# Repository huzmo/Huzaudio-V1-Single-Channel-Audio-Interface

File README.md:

# Huzaudio V1 - Single-Channel-Audio-Interface
The Huzaudio V1 can record musical instruments such as an electric or bass guitar through a standard 1/4" jack onto a computer through a USB-A port. 
|||
|:-:|:-:|

## Hardware
In order to select the right components, I created a diagram that depicted the process needed to complete the task at a high level and then found suitable ICs for each central task. These ICs served as "nodes" and related components and circuitry were selected in reference to manufacturer data sheets. Each component must be a suitable size to solder by hand but also small enough to maintain a compact form factor. 

The PCB was designed using KiCad, a free and open source EDA which provided the tools necessary to design my circuit. The schematic was designed to provide a lower-level representation of the initial flowchart and set the groundwork for a reliable PCB. Each of the squares on the above chart has been "translated" into circuitry and complementary components, such as decoupling capacitors and resistors, have been added. 

The main issue when it comes to mixed signal boards is signal integrity. Knowing this, a great amount of research was conducted to ensure that my board was able to protect the sensitive analog inputs. A 4-layer board was chosen with the following stackup:
| Layer    |   Purpose      |
| -------- |        ------- |
| Layer 1  | Analog Signal  |
| Layer 2  |  Power Plane   |
| Layer 3  |  Ground Plane  |
| Layer 4  | Digital Signal |

The ground plane in between the two signal layers ensures that they are shielded from one another while also providing a short current return path. Analog and digital components are physically segregated from one another, and the ADC serves as a bridge between the two signal types. The above considerations, as well as low-noise ICs ensure that the instrument signal receives little disruption throughout the circuit. 

## Software
Firmware for the audio interface must receive the converted digital signal via I2C from the analog-digital converter and send appropriately formatted packets to the computer. Software is written in C on the STM32F103C8T6 using the STM32CUBEIDE. The firmware is currently in development.

## Mechanical
The design for the case is straightforward to ensure functionality. An ample amount of room is provided to ensure that all components fit inside. To shield from EMI, the inside of the case is coated in a conductive material to ensure that EMI cannot leak nor enter and disrupt the sensitive analog signals.

## Simulation
To ensure my design worked before ordering the board, I ran some simulations using KiCad's built-in SPICE simulator. I tested if the input voltage regulators ensured stable power delivery and that the guitar input signal was amplified correctly as seen below.

## Next Steps
The design for this product was completed during an extended break from university and the prototyping for this project is projected to be held during the following semester break.

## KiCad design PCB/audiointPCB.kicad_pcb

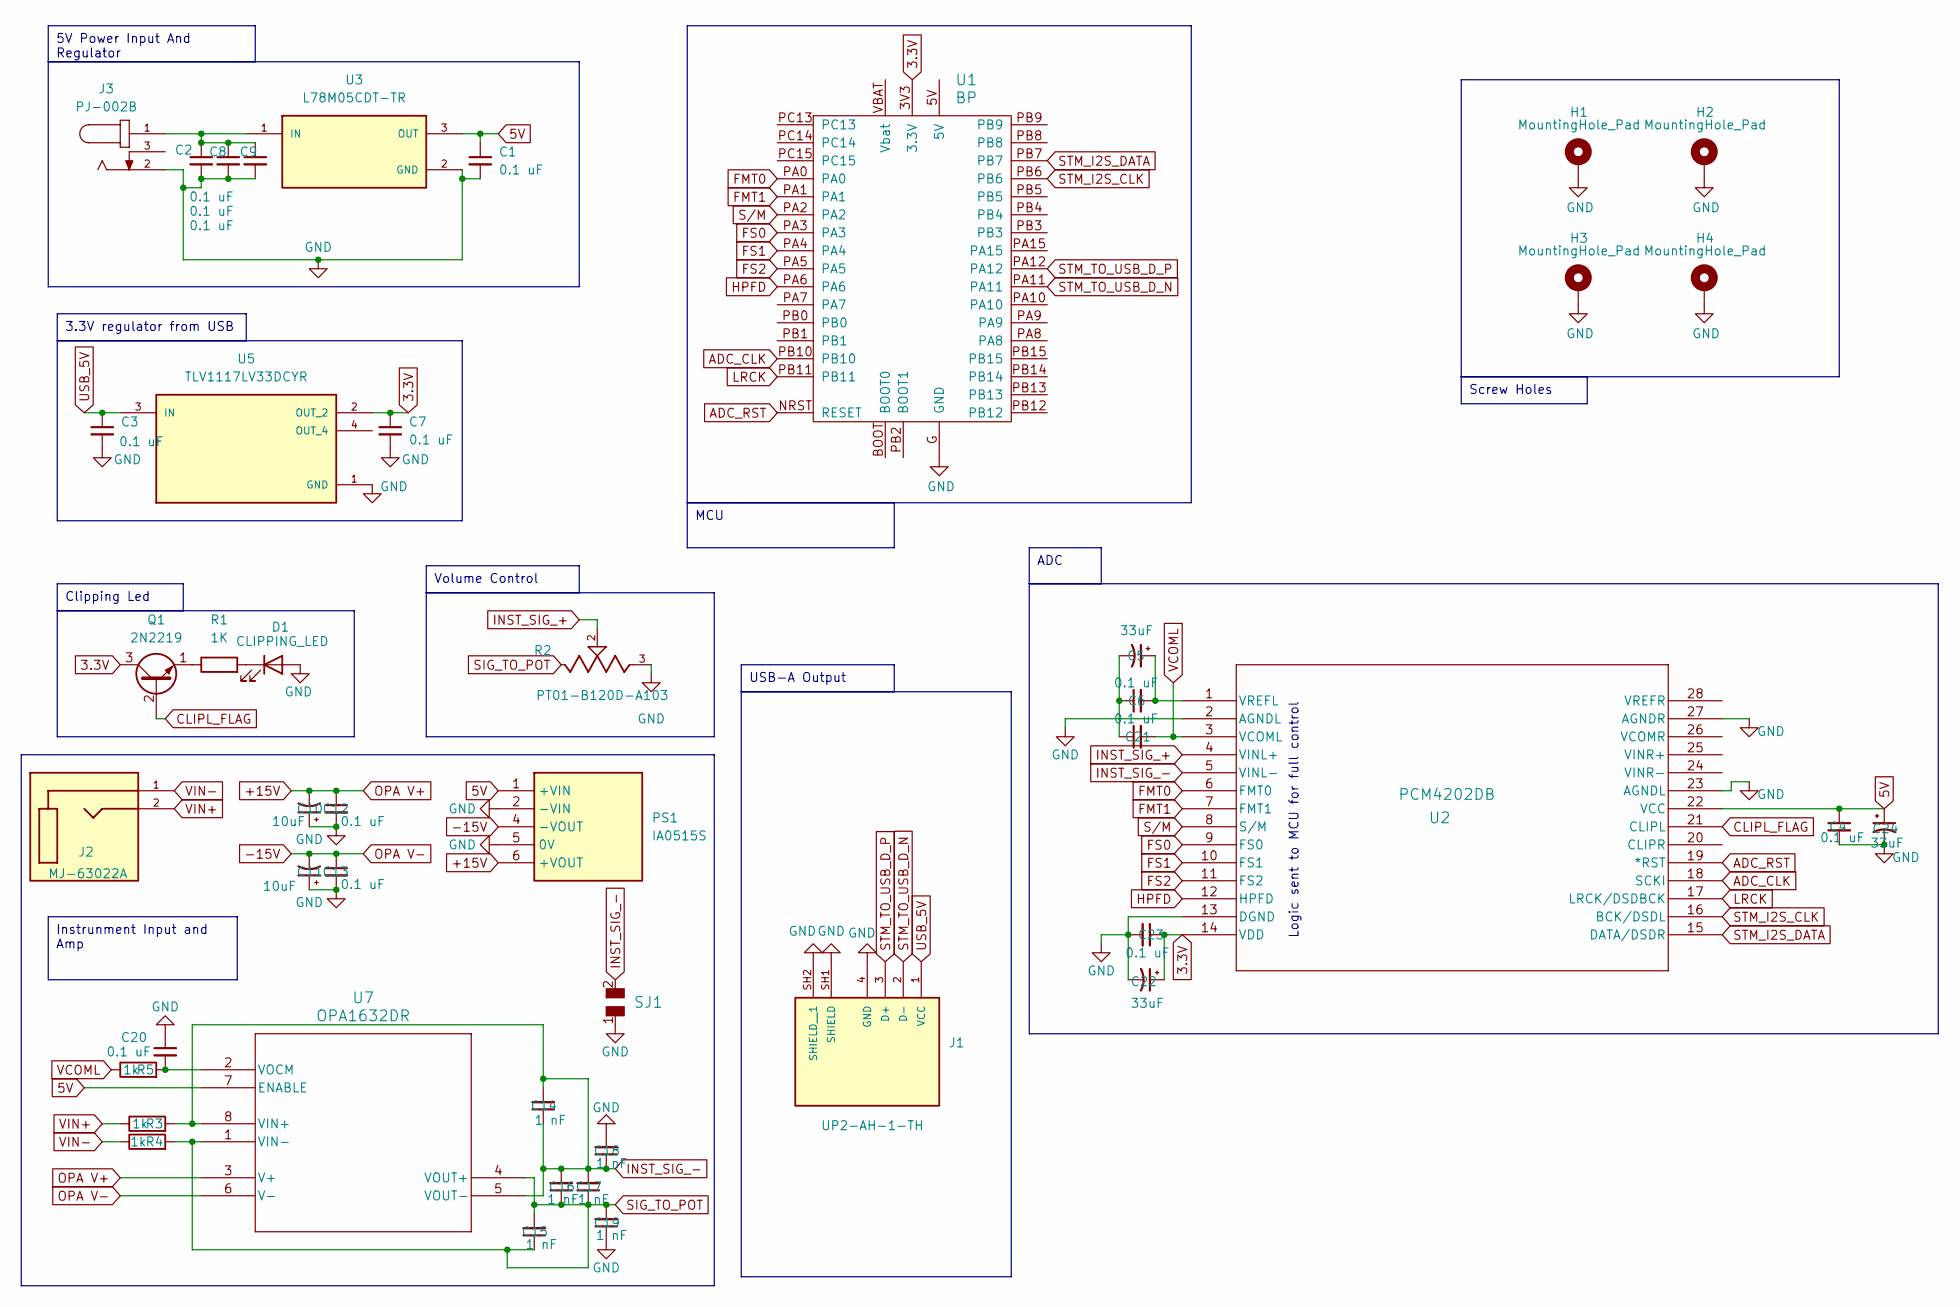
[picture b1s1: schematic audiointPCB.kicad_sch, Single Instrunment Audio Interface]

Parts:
C1, C2, C3, C4, C6, C7, C8, C9, C12, C13, C20, C21, C23: 0.1 uF; CAP_B32529_02.5X06.5X07.3_TDK
C5, C22, C24: 33uF; CAP_EEFK_C_PAN-L
C10, C11: 10uF; CAPC3216X180N
C14, C15, C16, C17, C18, C19: 1 nF; K104K10X7RF5UH5_VIS
D1: CLIPPING_LED; WL-TMRC_3MM
H1, H2, H3, H4: MountingHole_Pad; MountingHole_2mm
J1: UP2-AH-1-TH; CUI_UP2-AH-1-TH; PARTREV 1.05
J2: MJ-63022A; CUI_MJ-63022A; PARTREV 1.0
J3: PJ-002B; CUI_PJ-002B
PS1: IA0515S; Manufacturer_Part_Number IA0515S
Q1: 2N2219; TO-39-3
R1: 1K; RC1206N_YAG
R2: PT01-B120D-A103; TRIM_PT01-B120D-A103; PARTREV 1.0
R3, R4, R5: 1k; RC1206N_YAG
SJ1: SOLDER_JUMPER; SolderJumper-2_P1.3mm_Open_Pad1.0x1.5mm
U1: BP; blue_pill
U2: PCM4202DB; DB28
U3: L78M05CDT-TR; VREG_L78M05CDT-TR; PARTREV 24
U5: TLV1117LV33DCYR; VREG_TLV1117LV33DCYR; PARTREV B
U7: OPA1632DR; D8

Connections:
3.3V: C7.1, C22.1, C23.1, Q1.3 (C), U1.3V3 (3.3V), U2.14 (VDD), U5.2 (OUT_2)
5V: C1.1, C4.1, C24.1, PS1.1 (+VIN), U2.22 (VCC), U3.3 (OUT), U7.7 (ENABLE)
+15V: C10.2, C12.1, PS1.6 (+VOUT), U7.3 (V+)
-15V: C11.2, C13.1, PS1.4 (-VOUT), U7.6 (V-)
ADC_CLK: U1.PB10, U2.18 (SCKI)
ADC_RST: U1.NRST (RESET), U2.19 (*RST)
CLIPL_FLAG: Q1.2 (B), U2.21 (CLIPL)
FMT0: U1.PA0, U2.6 (FMT0)
FMT1: U1.PA1, U2.7 (FMT1)
FS0: U1.PA3, U2.9 (FS0)
FS1: U1.PA4, U2.10 (FS1)
FS2: U1.PA5, U2.11 (FS2)
GND: C1.2, C2.2, C3.2, C4.2, C7.2, C8.2, C9.2, C10.1, C11.1, C12.2, C13.2, C18.2, C19.1, C20.1, C22.2, C23.2, C24.2, D1.2 (A), H1.1, H2.1, H3.1, H4.1, J1.4 (GND), J1.SH1 (SHIELD), J1.SH2 (SHIELD__1), J3.2, PS1.2 (-VIN), PS1.5 (0V), R2.3, SJ1.1, U1.G (GND), U2.2 (AGNDL), U2.13 (DGND), U2.23 (AGNDL), U2.27 (AGNDR), U3.2 (GND), U5.1 (GND)
HPFD: U1.PA6, U2.12 (HPFD)
INST_SIG_+: R2.2, U2.4 (VINL+)
INST_SIG_-: C14.1, C14.2, C16.2, C17.2, C18.1, R3.2, SJ1.2, U2.5 (VINL-), U7.5 (VOUT-), U7.8 (VIN+)
LRCK: U1.PB11, U2.17 (LRCK/DSDBCK)
unnamed: C5.2, C6.1, C21.1
unnamed: D1.1 (K), R1.2
unnamed: Q1.1 (E), R1.1
unnamed: C5.1, C6.2, U2.1 (VREFL)
unnamed: C2.1, C8.1, C9.1, J3.1, U3.1 (IN)
unnamed: C20.2, R5.2, U7.2 (VOCM)
SIG_TO_POT: C15.1, C15.2, C16.1, C17.1, C19.2, R4.2, U7.1 (VIN-), U7.4 (VOUT+)
STM_I2S_CLK: U1.PB6, U2.16 (BCK/DSDL)
STM_I2S_DATA: U1.PB7, U2.15 (DATA/DSDR)
STM_TO_USB_D_N: J1.2 (D-), U1.PA11
STM_TO_USB_D_P: J1.3 (D+), U1.PA12
S/M: U1.PA2, U2.8 (S/M)
USB_5V: C3.1, J1.1 (VCC), U5.3 (IN)
VCOML: C21.2, R5.1, U2.3 (VCOML)
VIN+: J2.2, R3.1
VIN-: J2.1, R4.1

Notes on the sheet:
Screw Holes
USB-A Output
3.3V regulator from USB
Clipping Led
ADC
5V Power Input And Regulator
Volume Control
Instrunment Input and Amp
MCU
Logic sent to MCU for full control

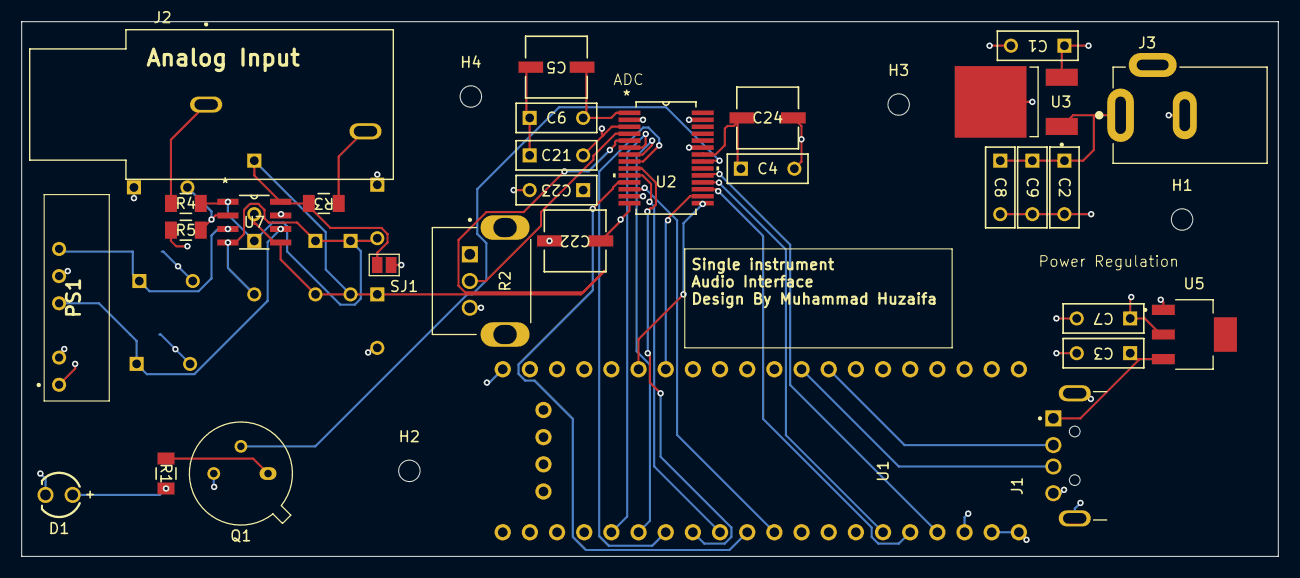
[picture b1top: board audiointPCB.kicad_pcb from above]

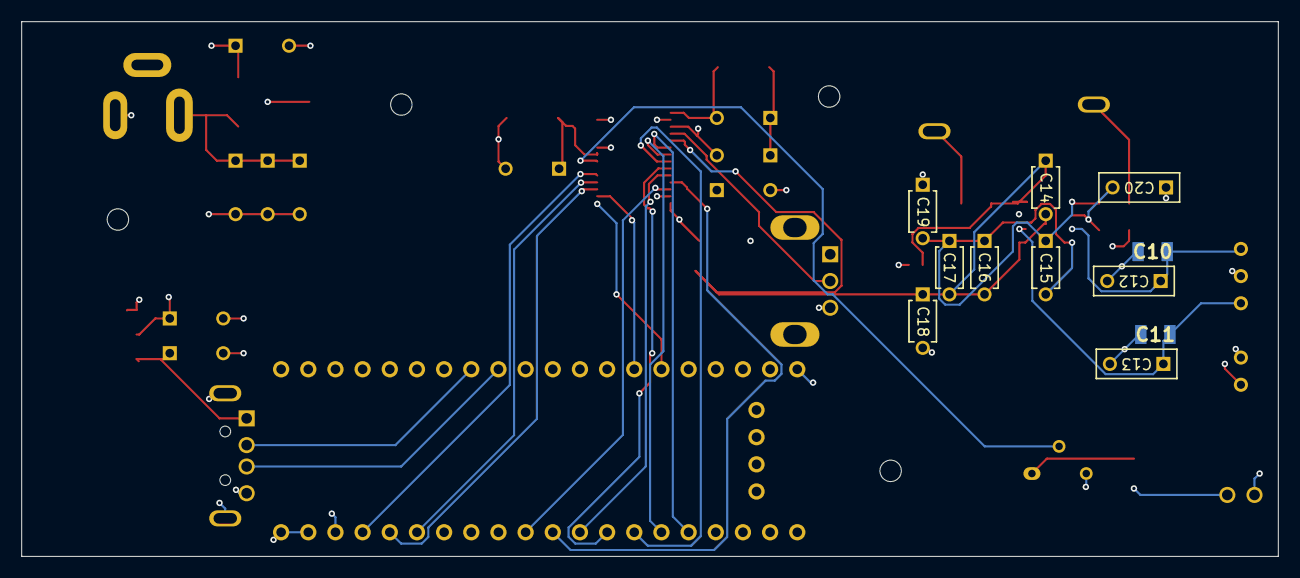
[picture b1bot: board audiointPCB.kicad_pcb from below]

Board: 4 copper layers, 117.5 x 50.0 mm, 45 parts (11 on the bottom side), 33 nets.

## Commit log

2024-11-18 Update README.md
    added images
2024-11-18 Create ignore
